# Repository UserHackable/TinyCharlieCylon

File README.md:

# TinyCharlieCylon
Files for the Tiny Charlie Cylon

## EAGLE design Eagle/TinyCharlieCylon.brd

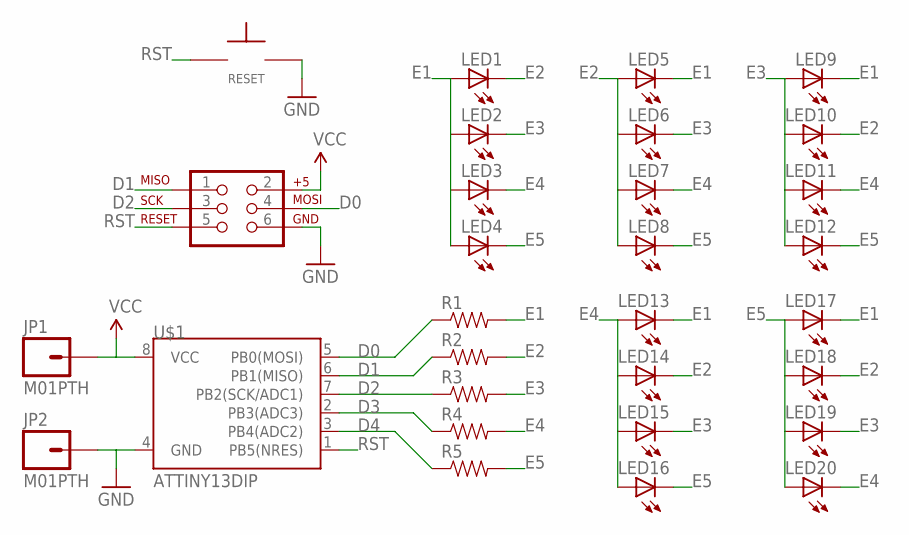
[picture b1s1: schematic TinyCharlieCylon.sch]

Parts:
J1: AVR_SPI_PRG_6PTH; 2X3
JP1, JP2: M01PTH; 1X01
LED1, LED2, LED3, LED4, LED5, LED6, LED7, LED8, LED9, LED10, LED11, LED12, LED13, LED14, LED15, LED16, LED17, LED18, LED19, LED20: LED3MM
R1, R2, R3, R4, R5: RESISTORAXIAL-0.3; AXIAL-0.3
RESET: TAC_SPST_NO
U$1: ATTINY13DIP; DIP08

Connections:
D0: J1.4, R1.P$1 (1), U$1.5 (PB0(MOSI))
D1: J1.1, R2.P$1 (1), U$1.6 (PB1(MISO))
D2: J1.3, R3.P$1 (1), U$1.7 (PB2(SCK/ADC1))
D3: R4.P$1 (1), U$1.2 (PB3(ADC3))
D4: R5.P$1 (1), U$1.3 (PB4(ADC2))
E1: LED1.A, LED2.A, LED3.A, LED4.A, LED5.K (C), LED9.K (C), LED13.K (C), LED17.K (C), R1.P$2 (2)
E2: LED1.K (C), LED5.A, LED6.A, LED7.A, LED8.A, LED10.K (C), LED14.K (C), LED18.K (C), R2.P$2 (2)
E3: LED2.K (C), LED6.K (C), LED9.A, LED10.A, LED11.A, LED12.A, LED15.K (C), LED19.K (C), R3.P$2 (2)
E4: LED3.K (C), LED7.K (C), LED11.K (C), LED13.A, LED14.A, LED15.A, LED16.A, LED20.K (C), R4.P$2 (2)
E5: LED4.K (C), LED8.K (C), LED12.K (C), LED16.K (C), LED17.A, LED18.A, LED19.A, LED20.A, R5.P$2 (2)
GND: J1.6, JP2.1, RESET.P$2, U$1.4 (GND)
RST: J1.5, RESET.P$1, U$1.1 (PB5(NRES))
VCC: J1.2, JP1.1, U$1.8 (VCC)

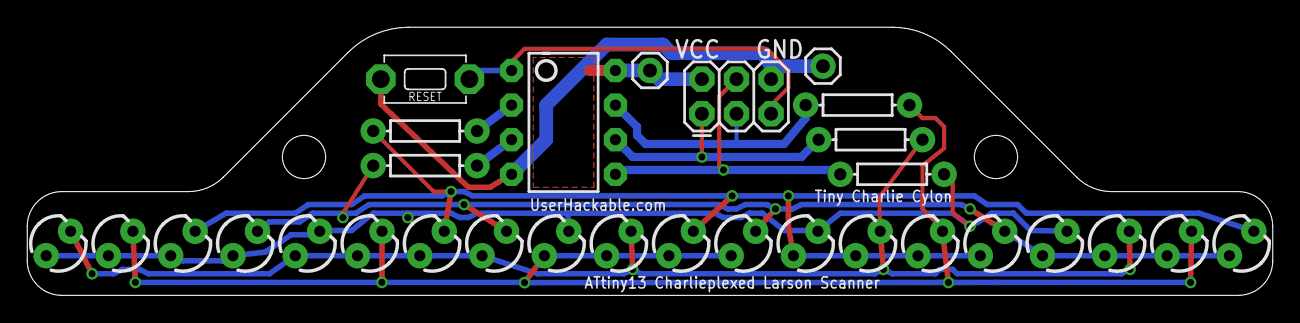
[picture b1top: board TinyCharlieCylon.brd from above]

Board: 2 copper layers, 91.4 x 19.7 mm, 30 parts (0 on the bottom side), 13 nets.

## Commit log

2015-10-25 Adding in board files

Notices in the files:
parts and their libraries:
SparkFun-LED: Licensing: Creative Commons ShareAlike 4.0 International - https://creativecommons.org/licenses/by-sa/4.0
